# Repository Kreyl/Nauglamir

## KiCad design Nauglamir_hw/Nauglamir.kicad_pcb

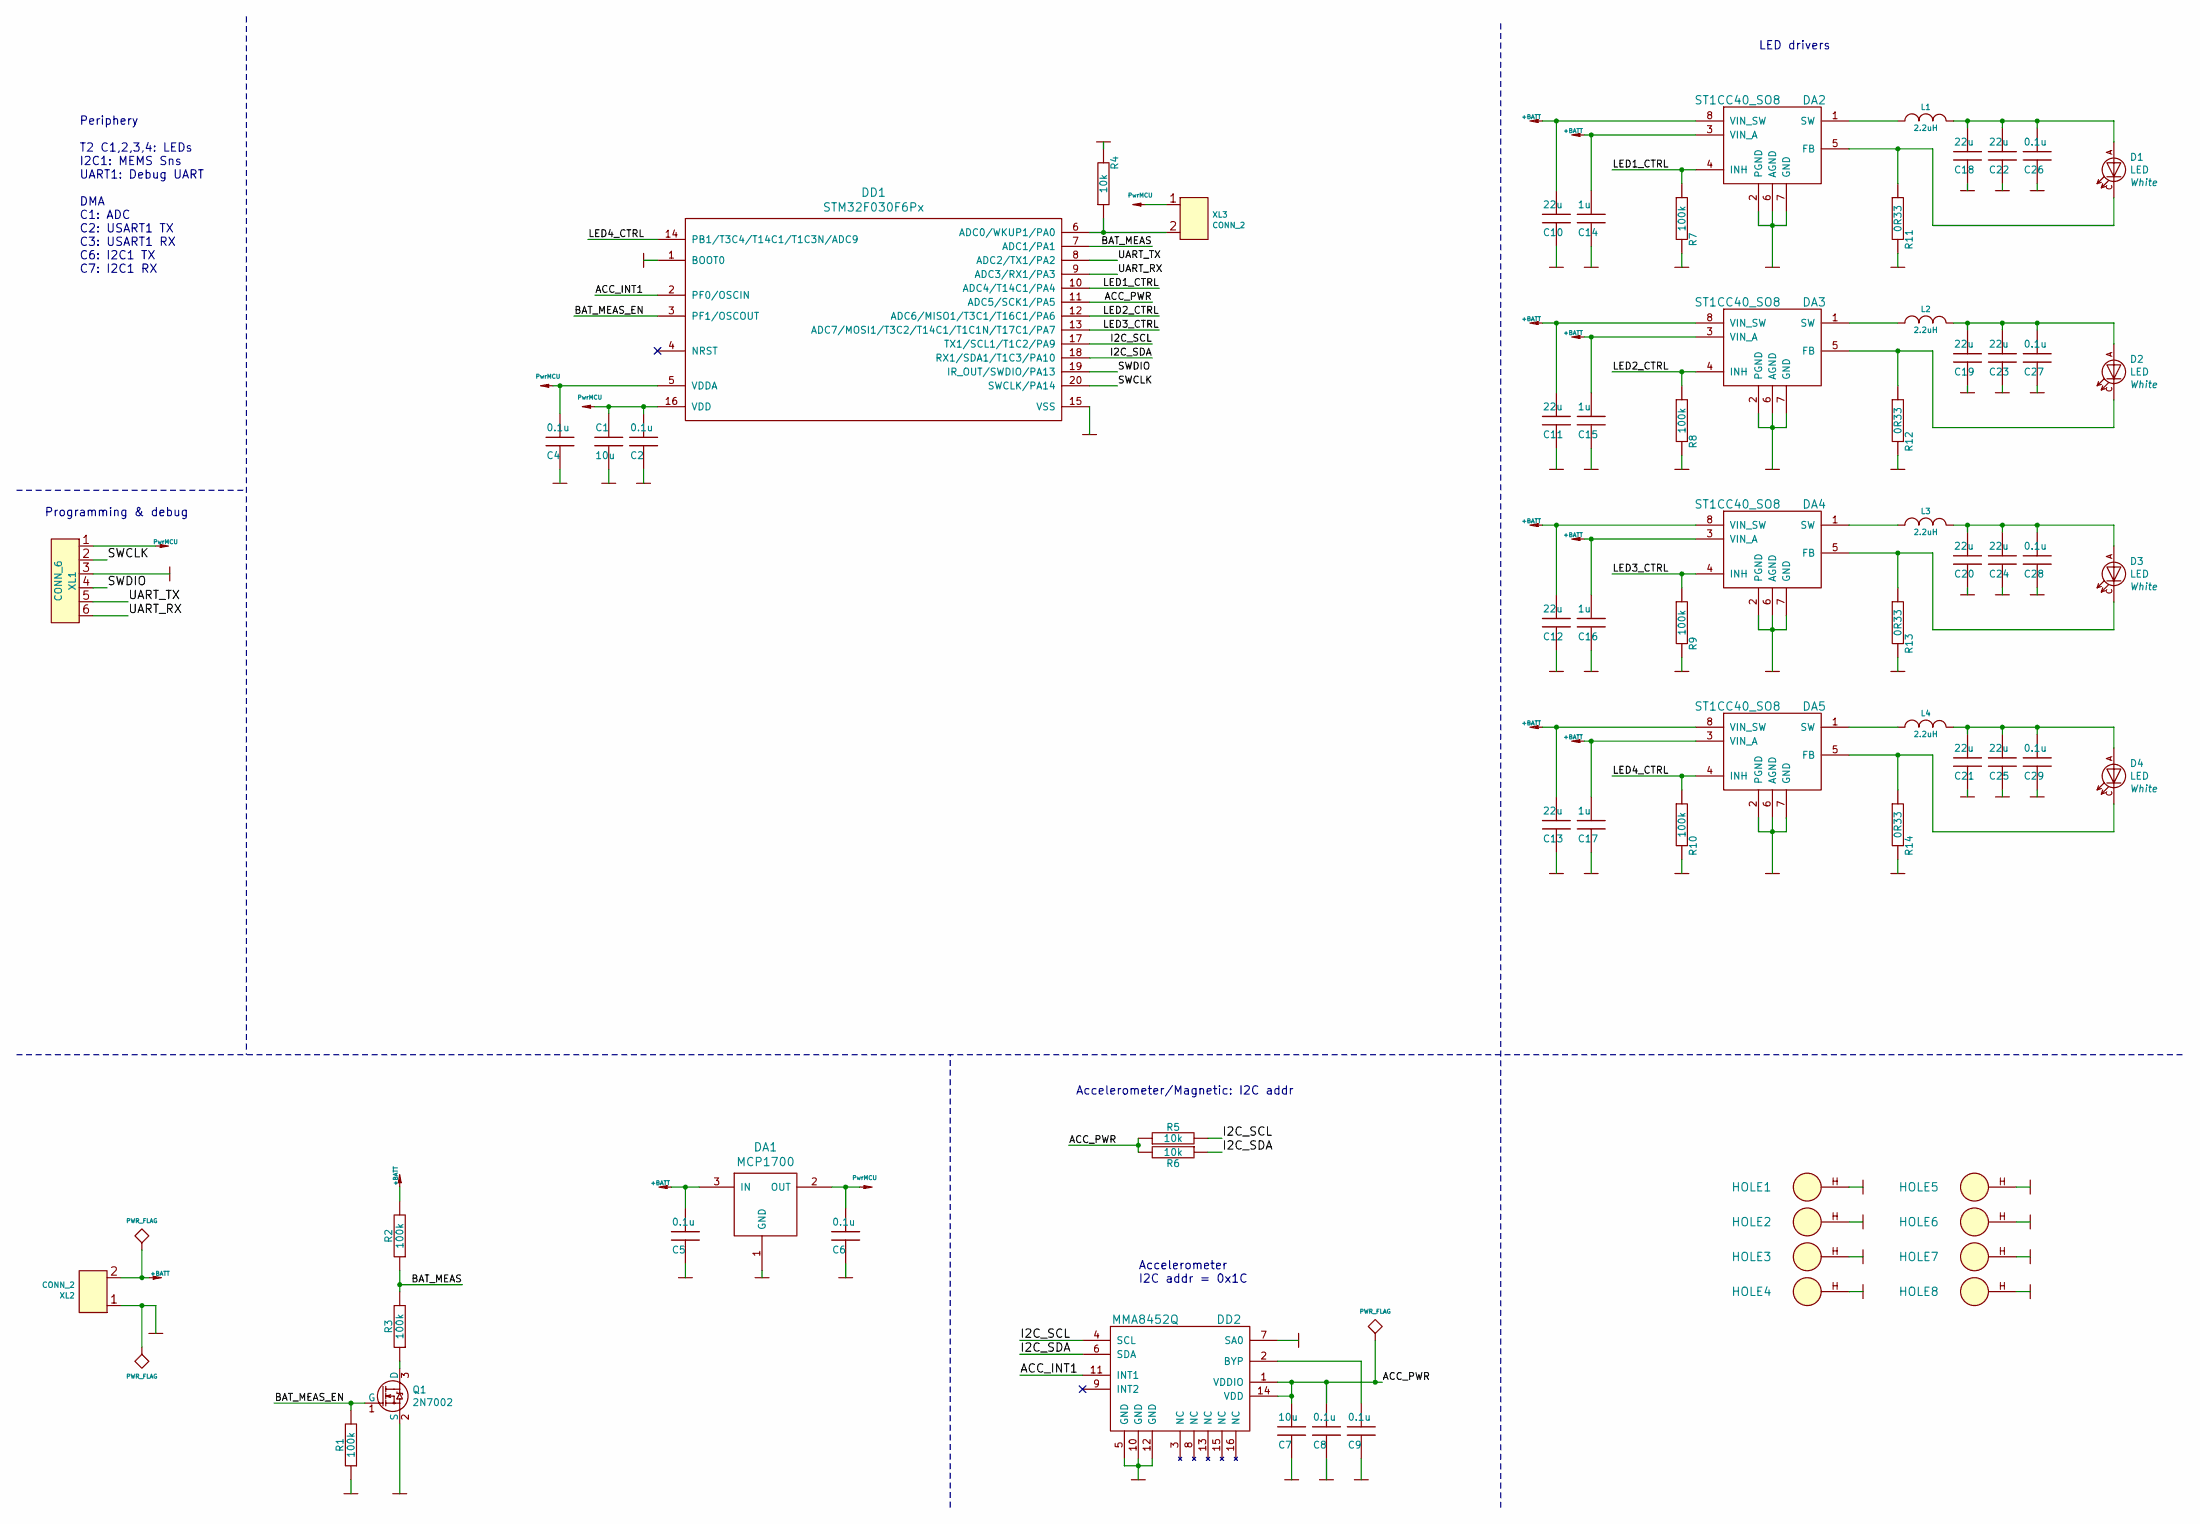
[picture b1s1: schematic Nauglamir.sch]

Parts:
C1, C7: 10u; CAP_0603_Silks
C2, C4, C5, C6, C8, C9, C26, C27, C28, C29: 0.1u; CAP_0603_Silks
C10, C11, C12, C13, C18, C19, C20, C21, C22, C23, C24, C25: 22u; CAP_0603_Silks
C14, C15, C16, C17: 1u; CAP_0603_Silks
D1, D2, D3, D4: LED; Cree_J3030
DA1: MCP1700; SOT23-3A
DA2, DA3, DA4, DA5: ST1CC40_SO8; SO8_150MIL
DD1: STM32F030F6Px; TSSOP20
DD2: MMA8452Q; QFN16_5x3
HOLE1, HOLE2, HOLE3, HOLE4, HOLE5, HOLE6, HOLE7, HOLE8: HOLE_METALLED; Hole2d2_out3d5mm
L1, L2, L3, L4: 2.2uH; IND_SRN2512
Q1: 2N7002; SOT23-3
R1, R2, R3, R7, R8, R9, R10: 100k; RES_0603
R4, R5, R6: 10k; RES_0603
R11, R12, R13, R14: 0R33; RES_1206
XL1: CONN_6; PLS-6
XL2, XL3: CONN_2; PBS-2

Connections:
+BATT: C5.1, C10.1, C11.1, C12.1, C13.1, C14.1, C15.1, C16.1, C17.1, DA1.3 (IN), DA2.3 (VIN_A), DA2.8 (VIN_SW), DA3.3 (VIN_A), DA3.8 (VIN_SW), DA4.3 (VIN_A), DA4.8 (VIN_SW), DA5.3 (VIN_A), DA5.8 (VIN_SW), R2.2, XL2.2 (PM)
/ACC_INT1: DD1.2 (PF0/OSCIN), DD2.11 (INT1)
/ACC_PWR: C7.1, C8.1, DD1.11 (ADC5/SCK1/PA5), DD2.1 (VDDIO), DD2.14 (VDD), R5.1, R6.2
/BAT_MEAS: DD1.7 (ADC1/PA1), R2.1, R3.2
/BAT_MEAS_EN: DD1.3 (PF1/OSCOUT), Q1.1 (G), R1.2
/I2C_SCL: DD1.17 (TX1/SCL1/T1C2/PA9), DD2.4 (SCL), R5.2
/I2C_SDA: DD1.18 (RX1/SDA1/T1C3/PA10), DD2.6 (SDA), R6.1
/LED1_CTRL: DA2.4 (INH), DD1.10 (ADC4/T14C1/PA4), R7.1
/LED2_CTRL: DA3.4 (INH), DD1.12 (ADC6/MISO1/T3C1/T16C1/PA6), R8.1
/LED3_CTRL: DA4.4 (INH), DD1.13 (ADC7/MOSI1/T3C2/T14C1/T1C1N/T17C1/PA7), R9.1
/LED4_CTRL: DA5.4 (INH), DD1.14 (PB1/T3C4/T14C1/T1C3N/ADC9), R10.1
/SWCLK: DD1.20 (SWCLK/PA14), XL1.2
/SWDIO: DD1.19 (IR_OUT/SWDIO/PA13), XL1.4
/UART_RX: DD1.9 (ADC3/RX1/PA3), XL1.6
/UART_TX: DD1.8 (ADC2/TX1/PA2), XL1.5
GND: C1.1, C2.2, C4.2, C5.2, C6.2, C7.2, C8.2, C9.2, C10.2, C11.2, C12.2, C13.2, C14.2, C15.2, C16.2, C17.2, C18.2, C19.2, C20.2, C21.2, C22.2, C23.2, C24.2, C25.2, C26.2, C27.2, C28.2, C29.2, DA1.1 (GND), DA2.2 (PGND), DA2.6 (AGND), DA2.7 (GND), DA3.2 (PGND), DA3.6 (AGND), DA3.7 (GND), DA4.2 (PGND), DA4.6 (AGND), DA4.7 (GND), DA5.2 (PGND), DA5.6 (AGND), DA5.7 (GND), DD1.1 (BOOT0), DD1.15 (VSS), DD2.5 (GND), DD2.7 (SA0), DD2.10 (GND), DD2.12 (GND), HOLE1.H, HOLE2.H, HOLE3.H, HOLE4.H, HOLE5.H, HOLE6.H, HOLE7.H, HOLE8.H, Q1.2 (S), R1.1, R4.2, R7.2, R8.2, R9.2, R10.2, R11.2, R12.2, R13.2, R14.2, XL1.3, XL2.1
unnamed: C9.1, DD2.2 (BYP)
unnamed: C18.1, C22.1, C26.1, D1.A, L1.1
unnamed: C19.1, C23.1, C27.1, D2.A, L2.1
unnamed: C20.1, C24.1, C28.1, D3.A, L3.1
unnamed: C21.1, C25.1, C29.1, D4.A, L4.1
unnamed: D1.C, DA2.5 (FB), R11.1
unnamed: D2.C, DA3.5 (FB), R12.1
unnamed: D3.C, DA4.5 (FB), R13.1
unnamed: D4.C, DA5.5 (FB), R14.1
unnamed: DA2.1 (SW), L1.2
unnamed: DA3.1 (SW), L2.2
unnamed: DA4.1 (SW), L3.2
unnamed: DA5.1 (SW), L4.2
unnamed: DD1.6 (ADC0/WKUP1/PA0), R4.1, XL3.2 (PM)
unnamed: Q1.3 (D), R3.1
PwrMCU: C1.2, C2.1, C4.1, C6.1, DA1.2 (OUT), DD1.5 (VDDA), DD1.16 (VDD), XL1.1, XL3.1

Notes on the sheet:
Accelerometer/Magnetic: I2C addr
Periphery T2 C1,2,3,4: LEDs I2C1: MEMS Sns UART1: Debug UART DMA C1: ADC C2: USART1 TX C3: USART1 RX C6: I2C1 TX C7: I2C1 RX
Programming & debug
Accelerometer I2C addr = 0x1C
LED drivers

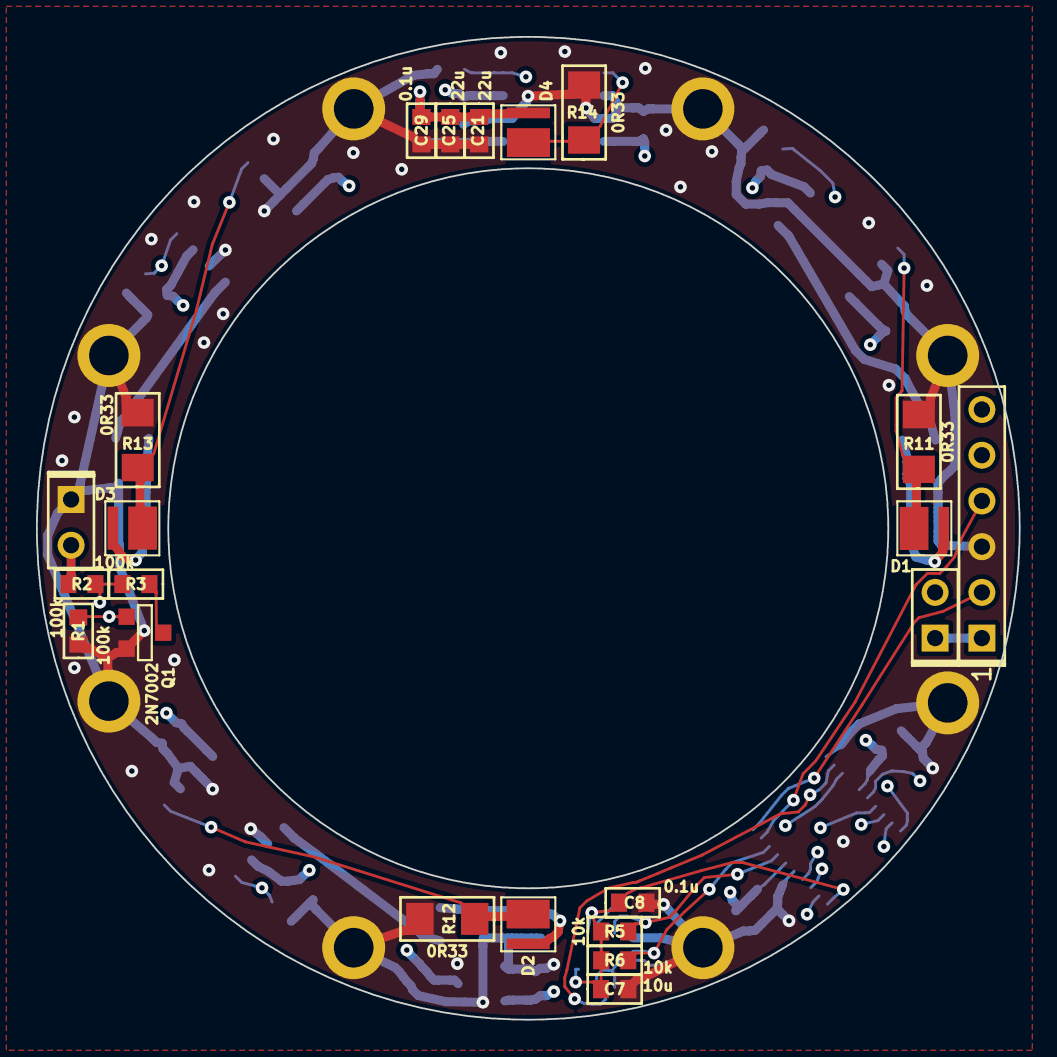
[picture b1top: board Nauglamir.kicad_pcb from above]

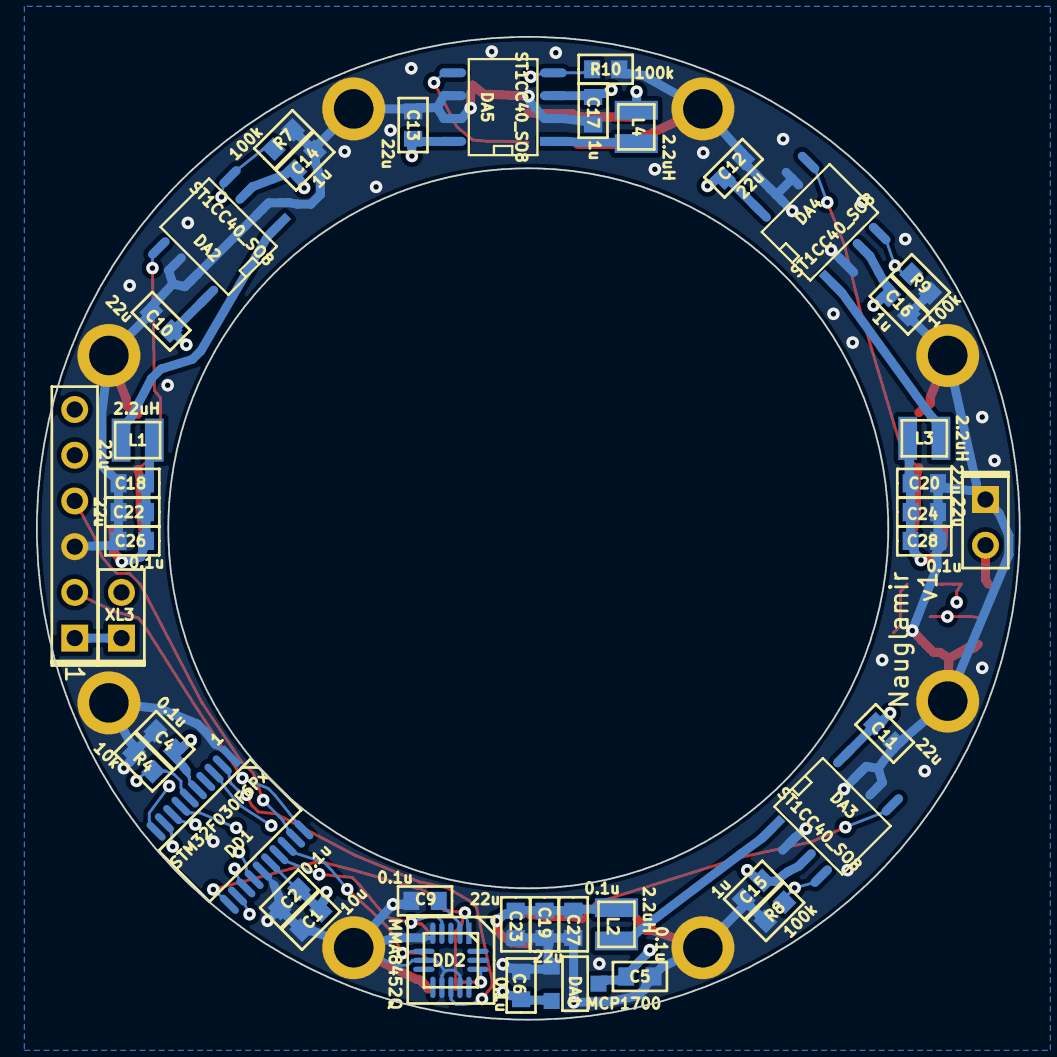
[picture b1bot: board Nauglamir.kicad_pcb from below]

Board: 4 copper layers, 54.6 x 54.6 mm, 69 parts (42 on the bottom side), 32 nets.

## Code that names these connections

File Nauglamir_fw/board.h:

#pragma once

// ==== General ====
#define BOARD_NAME          "Nauglamir1"
#define APP_NAME            "Nauglamir"

#define SIMPLESENSORS_ENABLED   FALSE

// MCU type as defined in the ST header.
#define STM32F030x6


/* ST driver system settings. */
#define STM32_ST_IRQ_PRIORITY               2
#define STM32_ST_USE_TIMER                  16

// Freq of external crystal if any. Leave it here even if not used.
#define CRYSTAL_FREQ_HZ     12000000

#define STM32_TIMCLK1       (Clk.APBFreqHz)
#define I2C1_ENABLED        TRUE
#define I2C_USE_SEMAPHORE   FALSE
#define ADC_REQUIRED        FALSE

#if 1 // ========================== GPIO =======================================
// PortMinTim_t: GPIO, Pin, Tim, TimChnl, invInverted, omPushPull, TopValue
// UART
#define UART_GPIO       GPIOA
#define UART_TX_PIN     2
#define UART_RX_PIN     3

// LEDs
#define LED1_PIN        { GPIOA, 4, TIM14, 1, invNotInverted, omPushPull, 255 }
#define LED2_PIN        { GPIOA, 6, TIM3,  1, invNotInverted, omPushPull, 255 }
#define LED3_PIN        { GPIOA, 7, TIM3,  2, invNotInverted, omPushPull, 255 }
#define LED4_PIN        { GPIOB, 1, TIM3,  4, invNotInverted, omPushPull, 255 }

// Acc mma8452
#define ACC_IRQ_GPIO    GPIOF
#define ACC_IRQ_PIN     0
#define ACC_PWR_PIN     GPIOA, 5

// I2C
#if I2C1_ENABLED
#define I2C1_GPIO       GPIOA
#define I2C1_SCL        9
#define I2C1_SDA        10
#define I2C_AF          AF4
#endif

#endif // GPIO

#if I2C1_ENABLED // ====================== I2C ================================
#define I2C1_BAUDRATE   400000
#define I2C_PILL        i2c1
#endif

#if ADC_REQUIRED // ======================= Inner ADC ==========================
// Clock divider: clock is generated from the APB2
#define ADC_CLK_DIVIDER     adcDiv2

// ADC channels
//#define BAT_CHNL          1

#define ADC_VREFINT_CHNL    17  // All 4xx, F072 and L151 devices. Do not change.
#define ADC_CHANNELS        { ADC_VREFINT_CHNL }
#define ADC_CHANNEL_CNT     1   // Do not use countof(AdcChannels) as preprocessor does not know what is countof => cannot check
#define ADC_SAMPLE_TIME     ast96Cycles
#define ADC_SAMPLE_CNT      8   // How many times to measure every channel

#define ADC_SEQ_LEN         (ADC_SAMPLE_CNT * ADC_CHANNEL_CNT)

#endif

#if 1 // =========================== DMA =======================================
#define STM32_DMA_REQUIRED  TRUE
// ==== Uart ====
#define UART_DMA_TX_MODE(Chnl) (STM32_DMA_CR_CHSEL(Chnl) | DMA_PRIORITY_LOW | STM32_DMA_CR_MSIZE_BYTE | STM32_DMA_CR_PSIZE_BYTE | STM32_DMA_CR_MINC | STM32_DMA_CR_DIR_M2P | STM32_DMA_CR_TCIE)
#define UART_DMA_RX_MODE(Chnl) (STM32_DMA_CR_CHSEL(Chnl) | DMA_PRIORITY_MEDIUM | STM32_DMA_CR_MSIZE_BYTE | STM32_DMA_CR_PSIZE_BYTE | STM32_DMA_CR_MINC | STM32_DMA_CR_DIR_P2M | STM32_DMA_CR_CIRC)
#define UART_DMA_TX     STM32_DMA_STREAM_ID(1, 4)
#define UART_DMA_RX     STM32_DMA_STREAM_ID(1, 5)
#define UART_DMA_CHNL   0   // Dummy

#if I2C1_ENABLED // ==== I2C ====
#define I2C1_DMA_TX     STM32_DMA_STREAM_ID(1, 2)
#define I2C1_DMA_RX     STM32_DMA_STREAM_ID(1, 3)
#define I2C1_DMA_CHNL   0   // Dummy
#endif

#if ADC_REQUIRED
#define ADC_DMA         STM32_DMA1_STREAM1
#define ADC_DMA_MODE    STM32_DMA_CR_CHSEL(0) |   /* dummy */ \
                        DMA_PRIORITY_LOW | \
                        STM32_DMA_CR_MSIZE_HWORD | \
                        STM32_DMA_CR_PSIZE_HWORD | \
                        STM32_DMA_CR_MINC |       /* Memory pointer increase */ \
                        STM32_DMA_CR_DIR_P2M |    /* Direction is peripheral to memory */ \
                        STM32_DMA_CR_TCIE         /* Enable Transmission Complete IRQ */
#endif // ADC

#endif // DMA

#if 1 // ========================== USART ======================================
#define PRINTF_FLOAT_EN FALSE
#define UART_TXBUF_SZ   256
#define UART_RXBUF_SZ   36

#define UARTS_CNT       1

#define CMD_UART_PARAMS \
    USART1, UART_GPIO, UART_TX_PIN, UART_GPIO, UART_RX_PIN, \
    UART_DMA_TX, UART_DMA_RX, UART_DMA_TX_MODE(UART_DMA_CHNL), UART_DMA_RX_MODE(UART_DMA_CHNL)

#endif

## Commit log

2019-06-02 Still F051
2019-06-03 PCB seems routed
2019-06-03 Routed
2019-06-03 + Gerbers sent to factory
2019-06-20 Proceeding w fw
2019-06-22 + Launched, uart works
2019-06-22 + Acc works
2019-06-22 + Leds ok, flicker seems ok
2019-06-22 + Average Result is not good
2019-06-23 * Algorythm RC
